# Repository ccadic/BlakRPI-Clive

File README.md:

# BlakRPI-Clive
BlakRPI Clive cyberdeck
GPL3

Please note this project is reserved to people with a minimum of electronic skills.
You need to know how to solder. 
You need to be able to make basic searches to find components by yourself
This is not an out of the box working pc

@sulfuroid

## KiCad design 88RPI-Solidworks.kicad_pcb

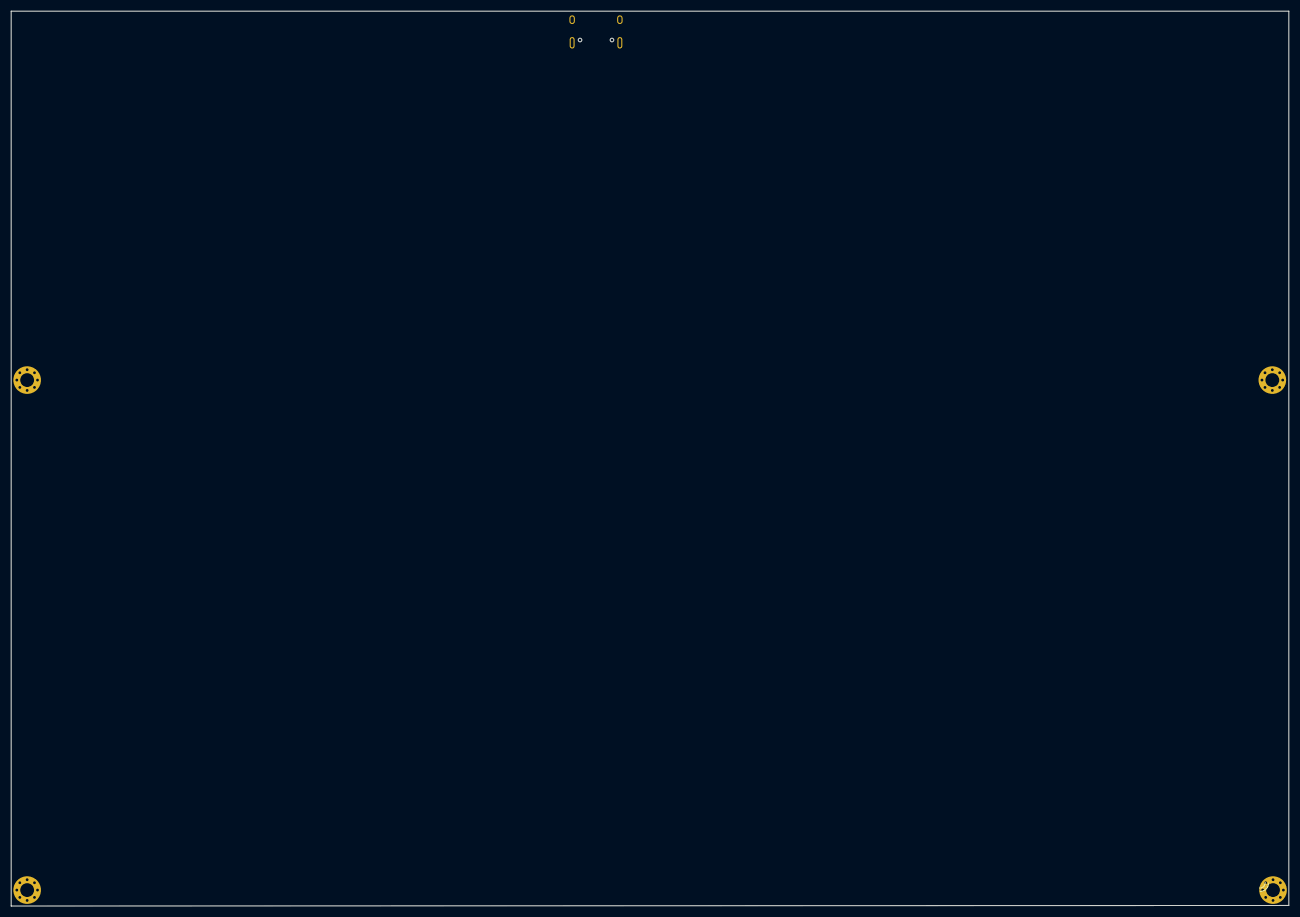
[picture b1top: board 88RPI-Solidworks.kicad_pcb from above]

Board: 2 copper layers, 231.3 x 162.0 mm, 5 parts (1 on the bottom side), 4 nets, no tracks yet.

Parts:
H1, H2, H3, H4: MountingHole; MountingHole_2.5mm_Pad_Via
J4: USBPOWER; GT-USB-7010

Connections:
/atmega/VBUS5v: J4.A4, J4.A9, J4.B4, J4.B9
GND: J4.A1, J4.A12, J4.B1, J4.B12, J4.S1
unnamed: J4.A6, J4.B6
unnamed: J4.A7, J4.B7
